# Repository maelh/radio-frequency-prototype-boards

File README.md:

# RF prototyping boards

When designing radio frequency (RF) circuits, we cannot rely on traditional perfboards or breadboards. Suitable boards need a [ground plane](https://en.wikipedia.org/wiki/Ground_plane#Printed_circuit_boards)  (essential for reducing noise in RF circuits), and should have minimal parasitic capacitances and inductances. Breadboards are especially unsuited, due to their RF circuit altering parasitics (mainly created by the horizontal signal rails, and the vertical power rails).

In the same vein, RF protoboards should support SMT components, which have less parasitic inductance compared to their leaded counterparts.

*This repository presents boards suitable for prototyping RF circuits, [ready to be sent](#fabricating-the-rf-proto-boards) to a PCB manufacturer.*

## Original work (ExpressPCB only)

[MegawattKS](https://www.youtube.com/@MegawattKS) gives an accessible [radio design lecture (YouTube)](https://www.youtube.com/watch?v=r_p7AHsSOdw&list=PL9Ox3wpnB0kqekAyz6blg4YdvoEMoJNJY), with [matching slides](https://ecefiles.org/radio-design-101-slides/), and an accompanying guide detailing [how to prototype RF circuits](https://ecefiles.org/rf-circuit-prototyping/).
It's quite a useful course for getting hands on experience and a non-math heavy intuition, using (comparatively) affordable tools, which are introduced as well: [NanoVNA and TinySA for radio design (YouTube)](https://www.youtube.com/watch?v=B7DFOq9rM_M&list=PL9Ox3wpnB0koBGofotI4xS8R0ct0FeYfv).

When you don't happen to have access to the very expensive RF equipment of a university laboratory, this course is ideal, as it was designed to measure and characterize the built RF circuits with the NanoVNA and the TinySA in mind. (Tools which are widely used in DIY/amateur communities, and accordingly have lots of documentation, tutorial videos, and useful addons available online.)

There is also a more advanced university level course ["Designing and Building Transmitters and Receivers"](https://ecefiles.org/rf-circuits-course-notes/) and its [part list](https://ecefiles.org/wp-content/uploads/2023/01/000b_ECE662_PartsList_F19.pdf).

Finally, MegawattKS kindly provided his [original design for ExpressPCB Plus](/original/RFprotoboard_Rev2_17nov22.rrb), which I used to take measurements of the various footprints and layout dimensions.

## Derived work (KiCad, many PCB manufacturers)

I faithfully redesigned the RF protoboard in KiCad, based on those measurements, to enable fabricating them with pretty much any PCB manufacturer.
The manual conversion was necessary, since the original boards are made for ExpressPCB, which uses a format exclusive to this manufacturer, with no export/import options. 

This resulted in two boards (out of the many variations I tried):

- The [standard version](/RF_ProtoBoard), with all the original dimensions and features being kept.

  <div align="center">
    
    <div>Front</div>    
  </div>

  <br/>

  <div align="center">
    
    <div>Back</div>
  </div>

- The [extended version](/RF_ProtoBoard_Extended), with the following changes compared to the standard version:
  - **added**: mounting holes
  - **added**: screw terminal for power (and pads to solder power wires onto)
  - **extended**: complete 4 pad U.FL connector footprints with silkscreen (for easier alignment)
  - **changed**: ground rings instead of a fully exposed ground plane
    - solder mask only exposes ground rings around the backside of plated through holes; ground rings should form nicer solder joints and hopefully ease solderability to the ground plane

  <br/>
  
  <div align="center">
    
    <div>Front</div>    
  </div>

  <br/>

  <div align="center">
    
    <div>Back</div>
  </div>
  
The screw terminal on the extended version reduces the amount of loose wires going off the board. Now, all the power wires from the 6 sub-modules can be routed to the centrally positioned pair of power pads, which have traces leading to the single central power screw terminal. The power pads on the backside of the board allow to add a decoupling/bulk capacitor.

## Fabricating the RF proto boards

The necessary ZIP files are available in the [fabrication directory](fabrication/), ready to be sent to a PCB manufacturer.
They are tuned for JLCPCB, but you can easily  [adjust the settings](Manufacturing.md#generating-files-manually) as needed when generating the Gerber, drill and map files from within the KiCad projects.

### PCB ordering website options

- *Extended board version:* inform your manufacturer to keep the silkscreen for the U.FL connectors, since it's on the bare PCB substrate (no solder mask underneath). To do so, write a note in the order page remark field: "Keep the silkscreen on the solder mask openings."
- Select "Untented" for "Via Covering".
- *JLCPCB only*: under "Remove Order Number", select "Specify a location". The "JLCJLCJLCJLC" text on the B.Silkscreen layer [specifies the location of the order number](https://jlcpcb.com/help/article/50-How-to-remove-order-number-from-your-PCB).

### Fabrication results, generating files manually, reviewing production files

I received my first extended RF protoboards on October 9, 2023. All tests indicate they are working well -- I made continuity tests with my multimeter -- and they were manufactured to specification regarding silkscreen, drilled hole diameters and correct through hole plating to the ground planes.

More details on how to generate Gerber files manually, my experiences with producing the extended board version, and how to review production files before fabrication begins, can be found under [manufacturing](Manufacturing.md).

## Soldering to the ground plane rings

In the first practical soldering tests, the ground ring design proved to be really easy to use for connecting pads to ground.

Either solder only to the inner ring on the backside to mechanically secure a through hole component to the board, without connecting it to the ground plane, or make a larger solder dome/blob that also covers the outer ground ring to make a ground plane connection.

No special or large sized tip is necessary: I use a 2 mm wide chisel tip, with my soldering station set to about 330°C, using Sn100Ni+ 0.5mm solder wire (see [recommended lead-free solder](NecessaryToolsAndParts.md#recommended-lead-free-solder)).

The only tricky part is to remove solder from the narrow plated through holes, so it is better to plan ahead if you want a throughhole component or a surface mount component on a specific pad.

### Soldering in more detail

Add some solder to the inner ring, then swirl the iron tip around the inner ring and the outer ground ring at the same time and add more solder to make a larger blob/dome. Initially it only bonds to the inner ring, but after a few seconds of swirling, the ground plane ring will also accept the solder. If the joint looks "cold"/crumbly, simply add a little flux and touch up the joint again briefly, so it will create a nice shiny joint.

### Removing a ground connection

Heat up a solder joint and collect excessive solder with the iron's tip, then brush it off on your brass wool cleaner. With less solder it will tend to only cover the inner ring, which means there is no more connection to ground.

Alternatively, use a solder sucker: keep the iron on the rings until the solder melts, then move the iron slightly off the center of the rings, but close enough, so it can keep the solder in a molten state. Then make the (silicone!) tip of the solder sucker touch directly the iron tip, and press the button of the desoldering pump to suck most of the solder away. It works quite reliably, and better than using solder wick.

The solder sucker tip should be made out of silicone, so it doesn't melt when touching the soldering iron.

## Parts and measurement equipment

Aside from measurement equipment, such as the NanoVNA and the TinySA, you will need U.FL connectors, screw terminals, and most importantly, surface mount components, to build RF circuits. See the [list of tools and parts needed](NecessaryToolsAndParts.md).

## Recommended literature

- RF Circuit Design 2nd Edition by Christopher Bowick
  - https://www.amazon.de/RF-Circuit-Design-Christopher-Bowick/dp/0750685182/
- [Ultimate Electronics - Conceptual Foundations of Electrical Engineering](https://ultimateelectronicsbook.com)
- [What is a VNA / Vector Network Analyzer by w2aew](https://www.youtube.com/watch?v=Sb3q8f0NBZc)
- [Basics of Capacitor & Inductor self-resonance, parasitics, etc. - Tutorial - w2aew](https://www.youtube.com/watch?v=vi24SpKYYoQ)
- [Measuring Self-Capacitance and Self-Resonant Frequency SRF of Inductors - KainkaLabs](https://www.youtube.com/watch?v=tjbK4LsOQRk)
- [Impedance Matching with the Smith Chart](https://www.youtube.com/watch?v=_pJ8kh0i2u4)
- https://www.tek.com/en/documents/primer/what-vector-network-analyzer-and-how-does-it-work
- Impedance Measurement Handbook -- A Guide to Measurement Technology and Techniques 
  - https://www.keysight.com/us/en/assets/7018-06840/application-notes/5950-3000.pdf
- https://hexandflex.com/2020/01/11/impedance-matching-with-qucs-studio-and-vna/
- https://www.gunthard-kraus.de/qucsstudio/Tutorial_Qucsstudio_V1-7_M%C3%A4rz%202019.pdf
- https://www.gunthard-kraus.de/fertig_NanoVNA/Deutsch/Nano_H_Deutsch_2020.pdf
- https://www.grund-wissen.de/elektronik/simulationen-mit-qucs.html
- https://electronics.stackexchange.com/questions/677822/s-parameters-calculation-from-vna-file
- https://qucs-help.readthedocs.io/de/qucs-0.0.18/start.html
- https://passive-components.eu/capacitors-losses-esrimpdfq/
- https://www.antenna-theory.com/tutorial/smith/chart.php
- https://groups.io/g/nanovna-users/files/C1-Smith_Chart_Aarhus_CAS_2010_caspers_version_20_September_2010.pdf
- https://www.intmath.com/complex-numbers/9-impedance-phase-angle.php
- https://www.microwaves101.com/encyclopedias/s-parameters
- https://www.baseapp.com/iot/antenna-tuning-for-beginners/
- Fixing calibration issues (see question comments): https://electronics.stackexchange.com/questions/609714/calibrating-a-vna
- Soldering skills and other factors affecting calibration: https://www.antune.net/calibration.html
- https://electronics.stackexchange.com/questions/602730/tuning-an-antenna-using-a-nanovna-smith-chart-and-impedance-readings
- [HP - S-Parameter Techniques for Faster, More Accurate Network Design](http://www.sss-mag.com/pdf/an-95-1.pdf)
- [Testing Inductors at Application Frequencies -- frequency dependent inductance, LCR meters vs VNAs](https://www.coilcraft.com/getmedia/917e2972-9585-4c8f-a94d-9a5b02fdffd9/doc119_testappfreq.pdf)
- [How to Use an LCR Meter: Basic Knowledge](https://www.hioki.com/global/learning/usage/lcr-meters_2.html)
- [Log Mag and Linear Mag (Keysight)](https://rfmw.em.keysight.com/wireless/helpfiles/89600B/WebHelp/subsystems/gui/Content/trace_format_logmag.htm)
- [LiteVNA vs. NanoVNA performance, noise, frenquency range with best accuracy](https://groups.io/g/liteVNA/message/1303)

## Useful software

- http://www.ae6ty.com/Smith_Charts.html
- https://w0qe.com/SimSmith.html
- http://www.physicsbox.com/indexsolveelec2en.html
- https://www.antune.net/
- https://www.atyune.com/

## Related perfboard designs

- https://github.com/electroniceel/protoboard
- https://github.com/jamesmunns/brick-mount
- https://github.com/hyves42/miniboard-protoboard
- https://github.com/mje-nz/protoboard
- https://github.com/AriaSalvatrice/synth-protoboard
- https://hackaday.com/2016/06/16/evaluating-the-unusual-and-innovative-perf-protoboard/
- https://www.busboard.com/SP3T-50x50-G-PTH
  - https://www.amazon.com/SP3T-50X50-G-PTH-SMTpads-3U-Thin-Plated-Ground-50x50mil/dp/B00LLPRNVW

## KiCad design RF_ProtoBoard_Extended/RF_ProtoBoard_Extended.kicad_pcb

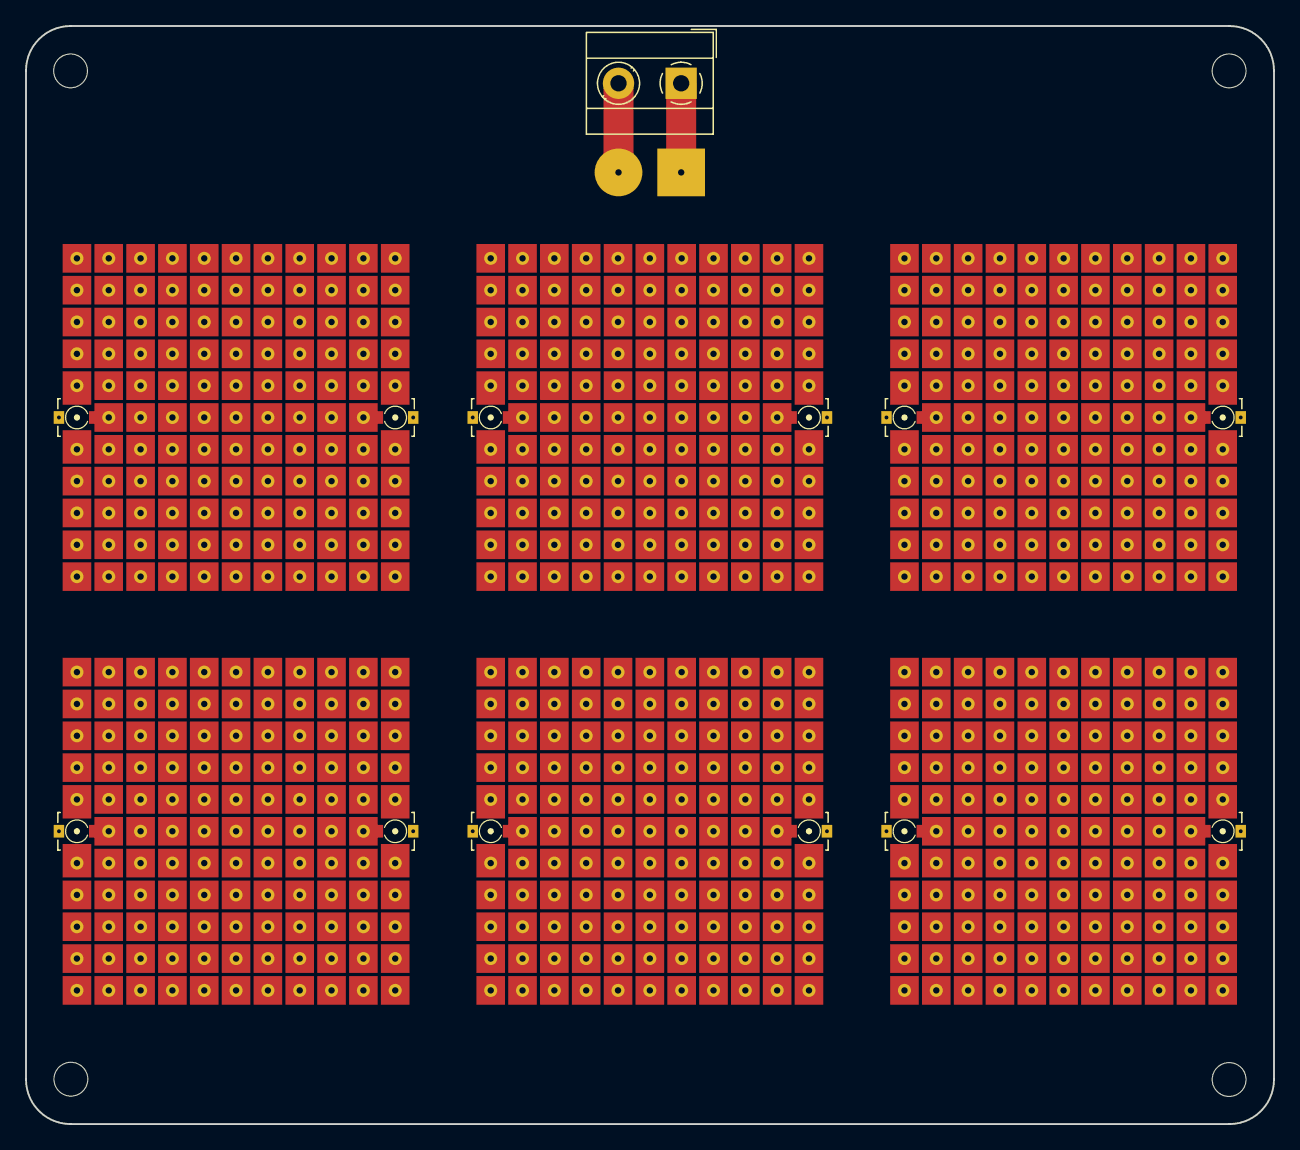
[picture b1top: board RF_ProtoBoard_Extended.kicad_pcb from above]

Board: 2 copper layers, 99.6 x 87.6 mm, 12 parts (0 on the bottom side), 8 nets.

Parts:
A1, A2, A3, A4, A5, A6: GndRing_RF_ProtoBoard_Module
H1, H2, H3, H4: MountingHole; MountingHole_2.7mm_M2.5_Clearance_1.7mm
J1: Screw_Terminal_01x02; TerminalBlock_MetzConnect_Type055_RT01502HDWU_1x02_P5.00mm_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
J2: Conn_VPlus_Gnd; VPlus_Gnd_Pads

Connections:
/Gnd: J1.1, J2.1
/V+: J1.2, J2.2
GND1: A1.0 (Pin_Gnd), A1.6a, A1.6k
GND2: A2.0 (Pin_Gnd), A2.6a, A2.6k
GND3: A3.0 (Pin_Gnd), A3.6a, A3.6k
GND4: A4.0 (Pin_Gnd), A4.6a, A4.6k
GND5: A5.0 (Pin_Gnd), A5.6a, A5.6k
GND6: A6.0 (Pin_Gnd), A6.6a, A6.6k

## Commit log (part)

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2023-09-17 Adapt plot settings
2023-09-18 add "JLCJLCJLCJLC" to back silkscreen layer, to specify location of JLCPCB order number
2023-09-19 Update gerber export options
2023-09-19 Update gerbers
2023-09-19 gerber -> gerbers
2023-09-19 Add PlotSettings.png
2023-09-19 Update plot settings
2023-09-19 Update fab zips
2023-09-25 Rename
2023-10-10 Add version number to the backside silkscreen
2023-10-10 Set PCB's revision variable, and automatically update back silkscreen accordingly
2023-10-10 Add ProductNumberPlaceholder text variable; makes it easier to change placeholder text (or entirely remove it) depending on manufacturer
2023-10-10 Normalize line endings
2023-11-21 Rename NanoVNA-Calibration.md to NanoVNA-Usage.md
2023-11-25 Add RF demo kit instructions
